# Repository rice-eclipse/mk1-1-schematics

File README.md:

# mk1-1-schematics
The official repository for mk1-1 pcb schematics for the Rice Eclipse Rocketry Club at Rice University.

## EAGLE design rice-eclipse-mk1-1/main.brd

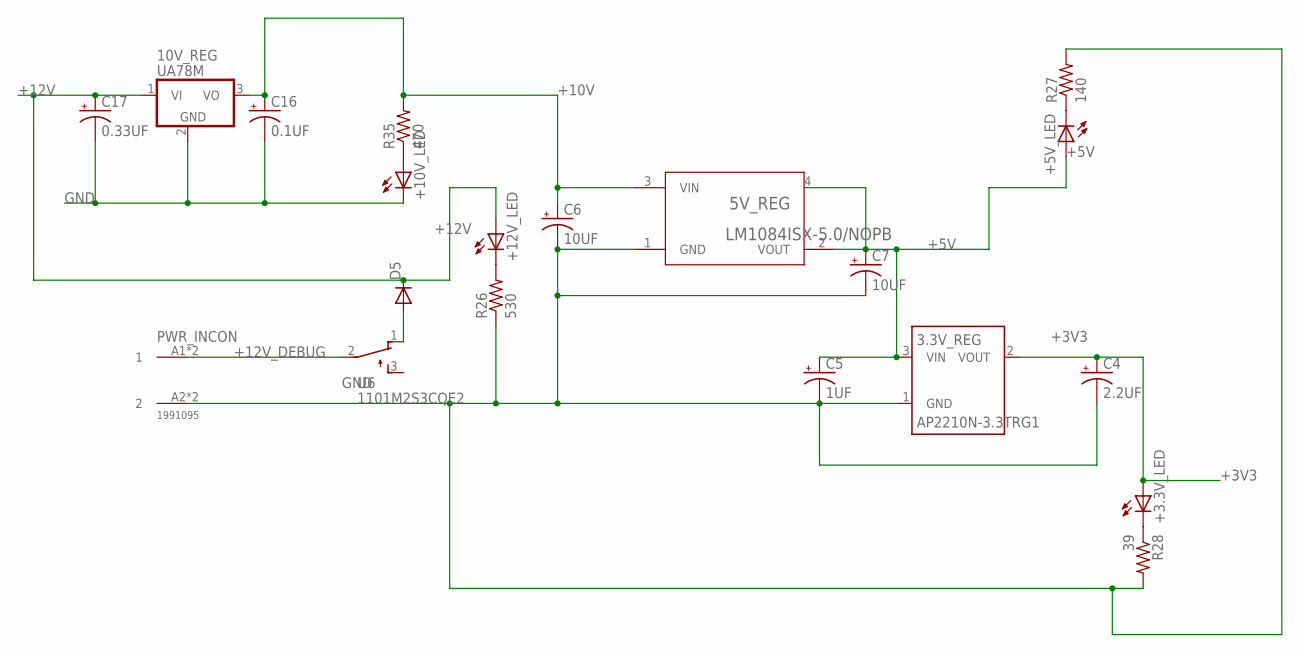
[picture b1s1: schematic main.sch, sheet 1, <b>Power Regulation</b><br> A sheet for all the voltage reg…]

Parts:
3.3V_REG: AP2210N-3.3TRG1; SOT23
5V_REG: LM1084ISX-5.0/NOPB; TS3B
10V_REG: UA78M; TO220S
+3.3V_LED, +5V_LED, +10V_LED, +12V_LED: LED5MM
C4: 2.2UF; E2,5-5
C5: 1UF; E2,5-5
C6, C7: 10UF; E2,5-5
C16: 0.1UF; E2,5-5
C17: 0.33UF; E2,5-5
D5: DIODE-DO201-15; DO201-15
PWR_IN: 1991095
R26: 530; R0805
R27: 140; R0805
R28: 39; R0805
R35: 470; R0805
U6: 1101M2S3CQE2

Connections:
+3V3: 3.3V_REG.2 (VOUT), +3.3V_LED.A, C4.+; also elsewhere on the board
+5V: 3.3V_REG.3 (VIN), 5V_REG.2 (VOUT), 5V_REG.4, +5V_LED.A, C5.+, C7.+; also elsewhere on the board
+10V: 5V_REG.3 (VIN), 10V_REG.3 (VO), C6.+, C16.+, R35.2; also elsewhere on the board
+12V: 10V_REG.1 (VI), +12V_LED.A, C17.+, D5.C; also elsewhere on the board
+12V_DEBUG: PWR_IN.A1 (1), PWR_IN.B1 (1), U6.2
GND: 3.3V_REG.1 (GND), 5V_REG.1 (GND), 10V_REG.2 (GND), +10V_LED.K (C), C4.-, C5.-, C6.-, C7.-, C16.-, C17.-, PWR_IN.A2 (2), PWR_IN.B2 (2), R26.1, R27.2, R28.2; also elsewhere on the board
unnamed: +12V_LED.K (C), R26.2
unnamed: +5V_LED.K (C), R27.1
unnamed: +3.3V_LED.K (C), R28.1
unnamed: D5.A, U6.1 (O)
unnamed: +10V_LED.A, R35.1

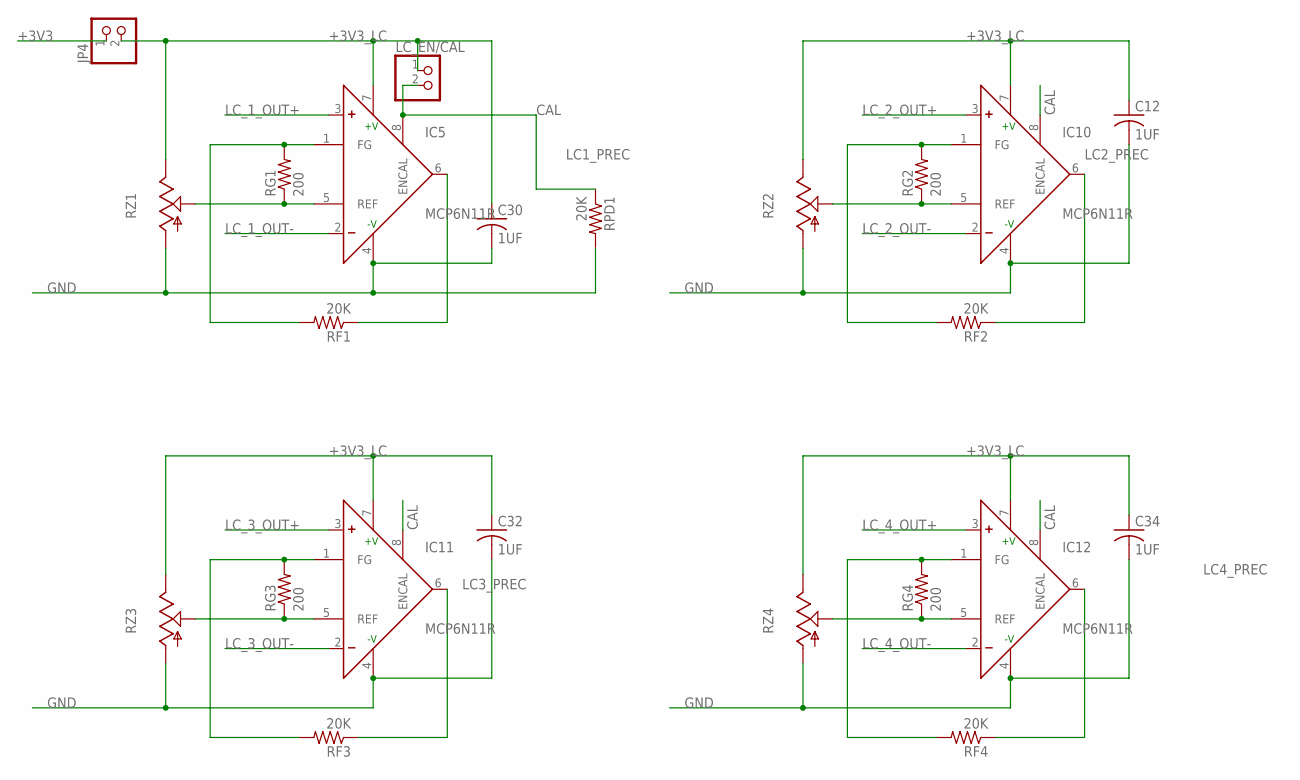
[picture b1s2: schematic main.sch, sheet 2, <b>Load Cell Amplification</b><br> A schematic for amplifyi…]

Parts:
C12, C30, C32, C34: 1UF; C0805
IC5, IC10, IC11, IC12: MCP6N11R; SO-8
JP4: PINHD-1X2; 1X02
LC_EN/CAL: PINHD-1X2; 1X02
RF1, RF2, RF3, RF4: 20K; R0805
RG1, RG2, RG3, RG4: 200; R0805
RPD1: 20K; R0805
RZ1, RZ2, RZ3, RZ4: TRIM_US-S64W; S64W

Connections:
+3V3: JP4.1; also elsewhere on the board
+3V3_LC: C12.1, C30.1, C32.1, C34.1, IC5.7 (+V), IC10.7 (+V), IC11.7 (+V), IC12.7 (+V), JP4.2, LC_EN/CAL.1, RZ1.E, RZ2.E, RZ3.E, RZ4.E
CAL: IC5.8 (ENCAL), IC10.8 (ENCAL), IC11.8 (ENCAL), IC12.8 (ENCAL), LC_EN/CAL.2, RPD1.1
GND: C12.2, C30.2, C32.2, C34.2, IC5.4 (-V), IC10.4 (-V), IC11.4 (-V), IC12.4 (-V), RPD1.2, RZ1.A, RZ2.A, RZ3.A, RZ4.A; also elsewhere on the board
LC1_PREC: IC5.6 (OUT), RF1.1; also elsewhere on the board
LC2_PREC: IC10.6 (OUT), RF2.1; also elsewhere on the board
LC3_PREC: IC11.6 (OUT), RF3.1; also elsewhere on the board
LC4_PREC: IC12.6 (OUT), RF4.1; also elsewhere on the board
LC_1_OUT+: IC5.3 (+); also elsewhere on the board
LC_1_OUT-: IC5.2 (-); also elsewhere on the board
LC_2_OUT+: IC10.3 (+); also elsewhere on the board
LC_2_OUT-: IC10.2 (-); also elsewhere on the board
LC_3_OUT+: IC11.3 (+); also elsewhere on the board
LC_3_OUT-: IC11.2 (-); also elsewhere on the board
LC_4_OUT+: IC12.3 (+); also elsewhere on the board
LC_4_OUT-: IC12.2 (-); also elsewhere on the board
unnamed: IC10.1 (FG), RF2.2, RG2.2
unnamed: IC10.5 (REF), RG2.1, RZ2.S
unnamed: IC11.1 (FG), RF3.2, RG3.2
unnamed: IC5.1 (FG), RF1.2, RG1.2
unnamed: IC5.5 (REF), RG1.1, RZ1.S
unnamed: IC11.5 (REF), RG3.1, RZ3.S
unnamed: IC12.1 (FG), RF4.2, RG4.2
unnamed: IC12.5 (REF), RG4.1, RZ4.S

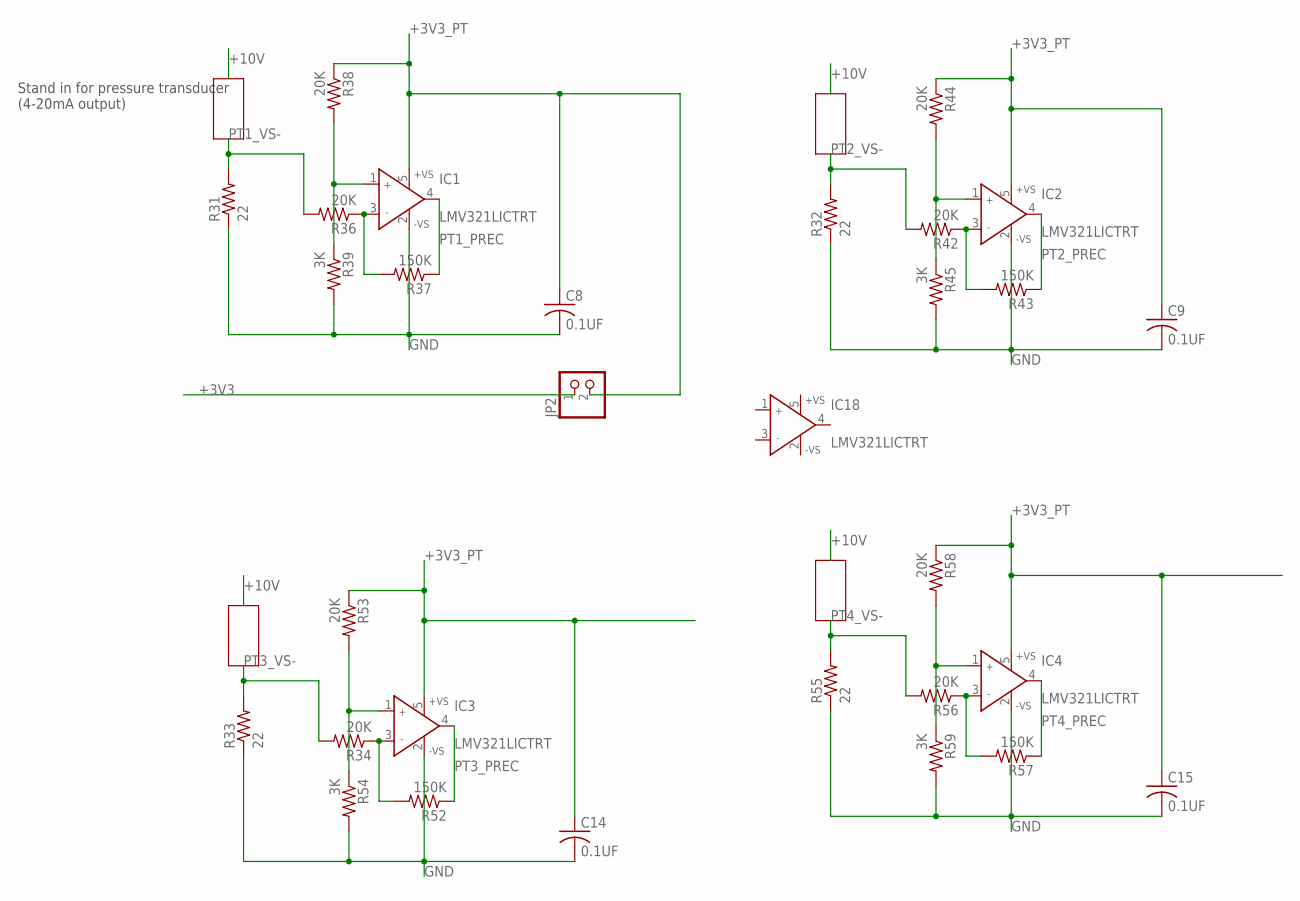
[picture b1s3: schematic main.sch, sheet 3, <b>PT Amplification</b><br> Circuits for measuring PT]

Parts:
C8, C9, C14, C15: 0.1UF; C0805
IC1, IC2, IC3, IC4, IC18: LMV321LICTRT; SOT23-5
JP2: PINHD-1X2; 1X02
R31, R32, R33, R55: 22; R0805
R34, R36, R38, R42, R44, R53, R56, R58: 20K; R0805
R37, R43, R52, R57: 150K; R0805
R39, R45, R54, R59: 3K; R0805

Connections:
+3V3: JP2.1; also elsewhere on the board
+3V3_PT: C8.1, C9.1, C14.1, C15.1, IC1.5 (+VS), IC2.5 (+VS), IC3.5 (+VS), IC4.5 (+VS), JP2.2, R38.1, R44.1, R53.1, R58.1
GND: C8.2, C9.2, C14.2, C15.2, IC1.2 (-VS), IC2.2 (-VS), IC3.2 (-VS), IC4.2 (-VS), R31.1, R32.1, R33.1, R39.2, R45.2, R54.2, R55.1, R59.2; also elsewhere on the board
unnamed: IC1.3 (IN-), R36.1, R37.2
unnamed: IC1.1 (IN+), R38.2, R39.1
unnamed: IC2.3 (IN-), R42.1, R43.2
unnamed: IC2.1 (IN+), R44.2, R45.1
unnamed: IC3.3 (IN-), R34.1, R52.2
unnamed: IC3.1 (IN+), R53.2, R54.1
unnamed: IC4.3 (IN-), R56.1, R57.2
unnamed: IC4.1 (IN+), R58.2, R59.1
PT1_PREC: IC1.4 (OUT), R37.1; also elsewhere on the board
PT1_VS-: R31.2, R36.2; also elsewhere on the board
PT2_PREC: IC2.4 (OUT), R43.1; also elsewhere on the board
PT2_VS-: R32.2, R42.2; also elsewhere on the board
PT3_PREC: IC3.4 (OUT), R52.1; also elsewhere on the board
PT3_VS-: R33.2, R34.2; also elsewhere on the board
PT4_PREC: IC4.4 (OUT), R57.1; also elsewhere on the board
PT4_VS-: R55.2, R56.2; also elsewhere on the board

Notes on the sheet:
Stand in for pressure transducer (4-20mA output)

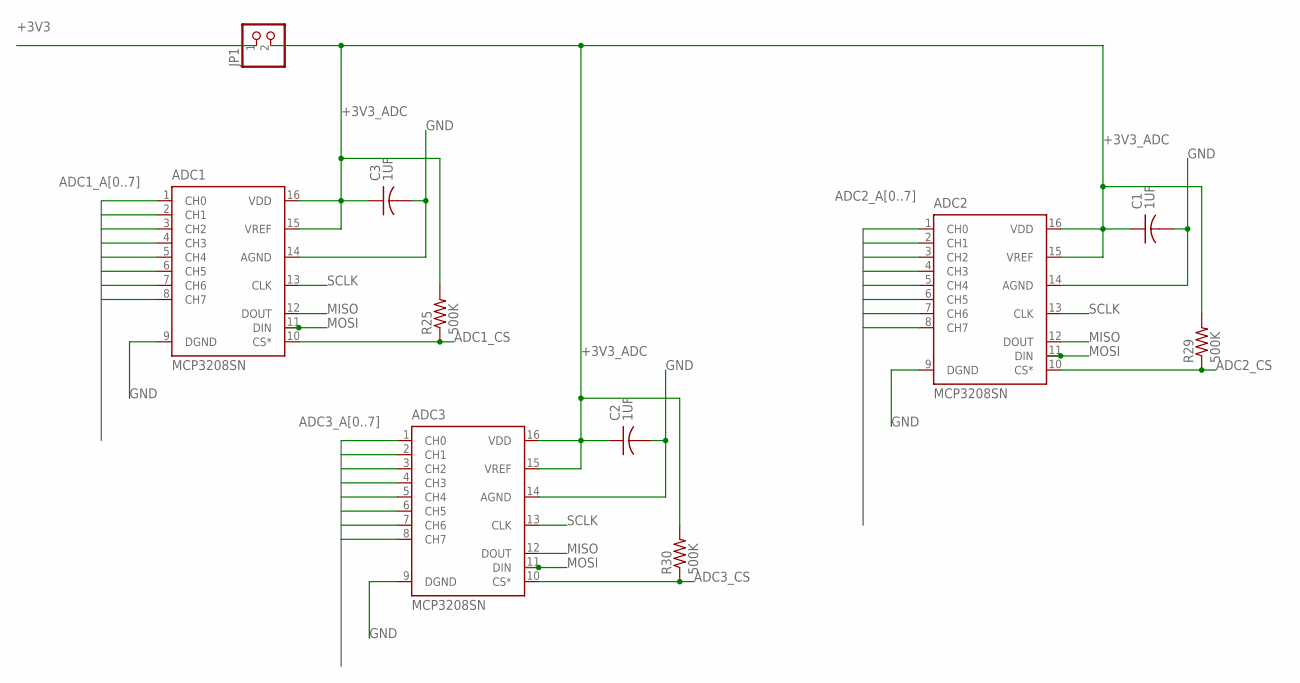
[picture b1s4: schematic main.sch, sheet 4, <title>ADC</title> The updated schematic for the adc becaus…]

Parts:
ADC1, ADC2, ADC3: MCP3208SN; SO-16
C1, C2, C3: 1UF; C0805
JP1: PINHD-1X2; 1X02
R25, R29, R30: 500K; R0805

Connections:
+3V3: JP1.1; also elsewhere on the board
+3V3_ADC: ADC1.15 (VREF), ADC1.16 (VDD), ADC2.15 (VREF), ADC2.16 (VDD), ADC3.15 (VREF), ADC3.16 (VDD), C1.1, C2.1, C3.1, JP1.2, R25.2, R29.2, R30.2
ADC1_A0: ADC1.1 (CH0); also elsewhere on the board
ADC1_A1: ADC1.2 (CH1); also elsewhere on the board
ADC1_A2: ADC1.3 (CH2); also elsewhere on the board
ADC1_A3: ADC1.4 (CH3); also elsewhere on the board
ADC1_A4: ADC1.5 (CH4); also elsewhere on the board
ADC1_A5: ADC1.6 (CH5); also elsewhere on the board
ADC1_A6: ADC1.7 (CH6); also elsewhere on the board
ADC1_A7: ADC1.8 (CH7); also elsewhere on the board
ADC1_CS: ADC1.10 (CS*), R25.1; also elsewhere on the board
ADC2_A0: ADC2.1 (CH0); also elsewhere on the board
ADC2_A1: ADC2.2 (CH1); also elsewhere on the board
ADC2_A2: ADC2.3 (CH2); also elsewhere on the board
ADC2_A3: ADC2.4 (CH3); also elsewhere on the board
ADC2_A4: ADC2.5 (CH4); also elsewhere on the board
ADC2_A5: ADC2.6 (CH5); also elsewhere on the board
ADC2_A6: ADC2.7 (CH6); also elsewhere on the board
ADC2_A7: ADC2.8 (CH7); also elsewhere on the board
ADC2_CS: ADC2.10 (CS*), R29.1; also elsewhere on the board
ADC3_A0: ADC3.1 (CH0); also elsewhere on the board
ADC3_A1: ADC3.2 (CH1); also elsewhere on the board
ADC3_A2: ADC3.3 (CH2); also elsewhere on the board
ADC3_A3: ADC3.4 (CH3); also elsewhere on the board
ADC3_A4: ADC3.5 (CH4); also elsewhere on the board
ADC3_A5: ADC3.6 (CH5); also elsewhere on the board
ADC3_A6: ADC3.7 (CH6); also elsewhere on the board
ADC3_A7: ADC3.8 (CH7); also elsewhere on the board
ADC3_CS: ADC3.10 (CS*), R30.1; also elsewhere on the board
GND: ADC1.9 (DGND), ADC1.14 (AGND), ADC2.9 (DGND), ADC2.14 (AGND), ADC3.9 (DGND), ADC3.14 (AGND), C1.2, C2.2, C3.2; also elsewhere on the board
MISO: ADC1.12 (DOUT), ADC2.12 (DOUT), ADC3.12 (DOUT); also elsewhere on the board
MOSI: ADC1.11 (DIN), ADC2.11 (DIN), ADC3.11 (DIN); also elsewhere on the board
SCLK: ADC1.13 (CLK), ADC2.13 (CLK), ADC3.13 (CLK); also elsewhere on the board

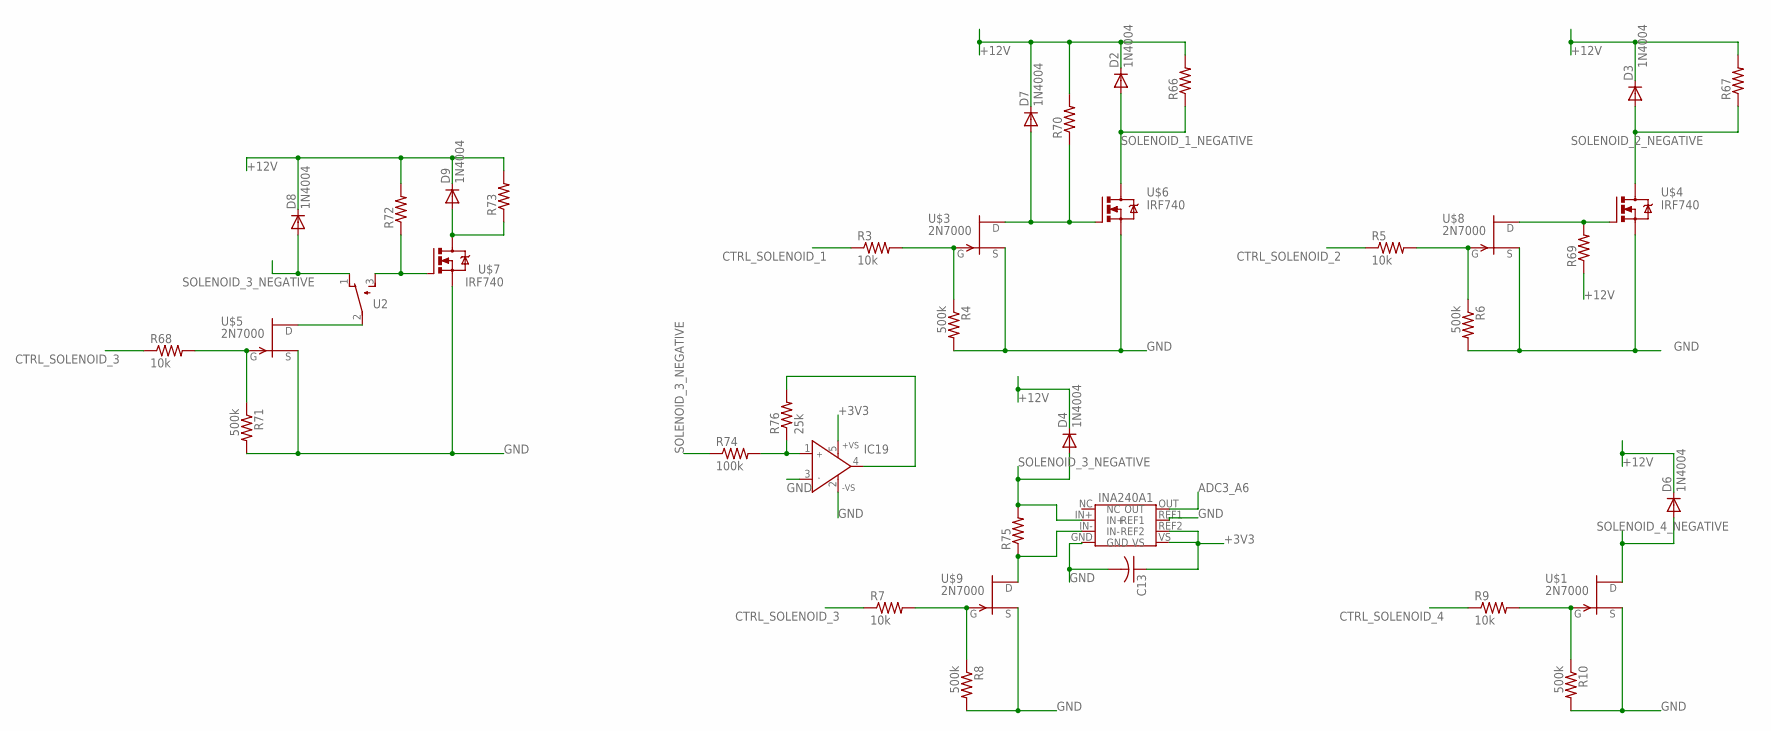
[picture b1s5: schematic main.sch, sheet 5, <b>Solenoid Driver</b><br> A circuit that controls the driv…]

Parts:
C13: C-USC0805; C0805
D2, D3, D4, D6, D7, D8, D9: 1N4004; DO41-10
IC19: LMV321LICTRT; SOT23-5
R3, R5, R7, R9, R68: 10k; R0805
R4, R6, R8, R10, R71: 500k; R0805
R66, R67, R69, R70, R72, R73: R-US_R0805; R0805
R74: 100k; R0805
R75: R-US_R0603; R0603
R76: 25k; R0805
U2: 1101M2S3CQE2
U$1, U$3, U$5, U$8, U$9: 2N7000; SOT23
U$4, U$6, U$7: IRF740; TO220BV
U$10: INA240A1

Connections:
+3V3: C13.1, IC19.5 (+VS), U$10.REF2, U$10.VS; also elsewhere on the board
+12V: D2.C, D3.C, D4.C, D6.C, D7.C, D8.C, D9.C, R66.2, R67.2, R69.1, R70.2, R72.2, R73.2; also elsewhere on the board
ADC3_A6: U$10.OUT; also elsewhere on the board
CTRL_SOLENOID_1: R3.1; also elsewhere on the board
CTRL_SOLENOID_2: R5.1; also elsewhere on the board
CTRL_SOLENOID_3: R7.1, R68.1; also elsewhere on the board
CTRL_SOLENOID_4: R9.1; also elsewhere on the board
GND: C13.2, IC19.2 (-VS), IC19.3 (IN-), R4.2, R6.2, R8.2, R10.2, R71.2, U$1.2 (S), U$3.2 (S), U$4.S, U$5.2 (S), U$6.S, U$7.S, U$8.2 (S), U$9.2 (S), U$10.GND, U$10.REF1; also elsewhere on the board
unnamed: R3.2, R4.1, U$3.1 (G)
unnamed: R5.2, R6.1, U$8.1 (G)
unnamed: R7.2, R8.1, U$9.1 (G)
unnamed: R9.2, R10.1, U$1.1 (G)
unnamed: D7.A, R70.1, U$3.3 (D), U$6.G
unnamed: R68.2, R71.1, U$5.1 (G)
unnamed: R69.2, U$4.G, U$8.3 (D)
unnamed: U2.2, U$5.3 (D)
unnamed: R72.1, U2.3 (S), U$7.G
unnamed: D9.A, R73.1, U$7.D
unnamed: R75.1, U$9.3 (D), U$10.IN-
unnamed: IC19.1 (IN+), R74.2, R76.1
unnamed: IC19.4 (OUT), R76.2
SOLENOID_1_NEGATIVE: D2.A, R66.1, U$6.D; also elsewhere on the board
SOLENOID_2_NEGATIVE: D3.A, R67.1, U$4.D; also elsewhere on the board
SOLENOID_3_NEGATIVE: D4.A, D8.A, R74.1, R75.2, U2.1 (O), U$10.IN+; also elsewhere on the board
SOLENOID_4_NEGATIVE: D6.A, U$1.3 (D); also elsewhere on the board

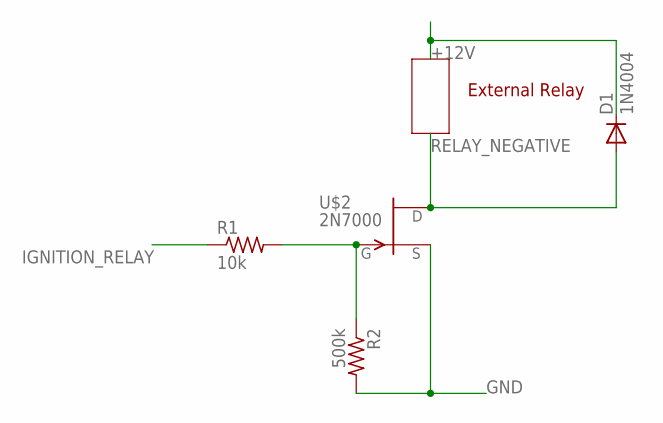
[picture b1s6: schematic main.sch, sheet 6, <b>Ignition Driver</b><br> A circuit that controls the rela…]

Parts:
D1: 1N4004; DO41-10
R1: 10k; R0805
R2: 500k; R0805
U$2: 2N7000; SOT23

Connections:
+12V: D1.C; also elsewhere on the board
GND: R2.2, U$2.2 (S); also elsewhere on the board
IGNITION_RELAY: R1.1; also elsewhere on the board
unnamed: R1.2, R2.1, U$2.1 (G)
RELAY_NEGATIVE: D1.A, U$2.3 (D); also elsewhere on the board

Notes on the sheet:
External Relay

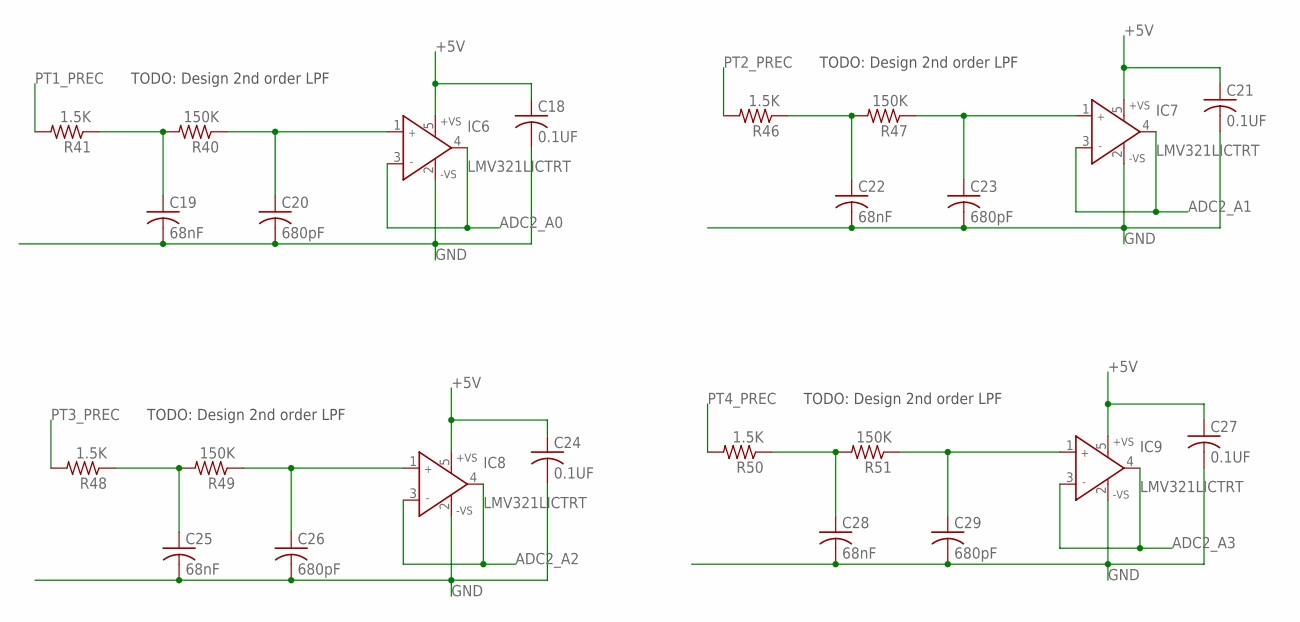
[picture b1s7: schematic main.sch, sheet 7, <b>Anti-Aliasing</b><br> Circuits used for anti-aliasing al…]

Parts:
C18, C21, C24, C27: 0.1UF; C0805
C19, C22, C25, C28: 68nF; C0805
C20, C23, C26, C29: 680pF; C0805
IC6, IC7, IC8, IC9: LMV321LICTRT; SOT23-5
R40, R47, R49, R51: 150K; R0805
R41, R46, R48, R50: 1.5K; R0805

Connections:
+5V: C18.1, C21.1, C24.1, C27.1, IC6.5 (+VS), IC7.5 (+VS), IC8.5 (+VS), IC9.5 (+VS); also elsewhere on the board
ADC2_A0: IC6.3 (IN-), IC6.4 (OUT); also elsewhere on the board
ADC2_A1: IC7.3 (IN-), IC7.4 (OUT); also elsewhere on the board
ADC2_A2: IC8.3 (IN-), IC8.4 (OUT); also elsewhere on the board
ADC2_A3: IC9.3 (IN-), IC9.4 (OUT); also elsewhere on the board
GND: C18.2, C19.2, C20.2, C21.2, C22.2, C23.2, C24.2, C25.2, C26.2, C27.2, C28.2, C29.2, IC6.2 (-VS), IC7.2 (-VS), IC8.2 (-VS), IC9.2 (-VS); also elsewhere on the board
unnamed: C19.1, R40.2, R41.1
unnamed: C20.1, IC6.1 (IN+), R40.1
unnamed: C22.1, R46.1, R47.2
unnamed: C23.1, IC7.1 (IN+), R47.1
unnamed: C25.1, R48.1, R49.2
unnamed: C26.1, IC8.1 (IN+), R49.1
unnamed: C28.1, R50.1, R51.2
unnamed: C29.1, IC9.1 (IN+), R51.1
PT1_PREC: R41.2; also elsewhere on the board
PT2_PREC: R46.2; also elsewhere on the board
PT3_PREC: R48.2; also elsewhere on the board
PT4_PREC: R50.2; also elsewhere on the board

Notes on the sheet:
TODO: Design 2nd order LPF

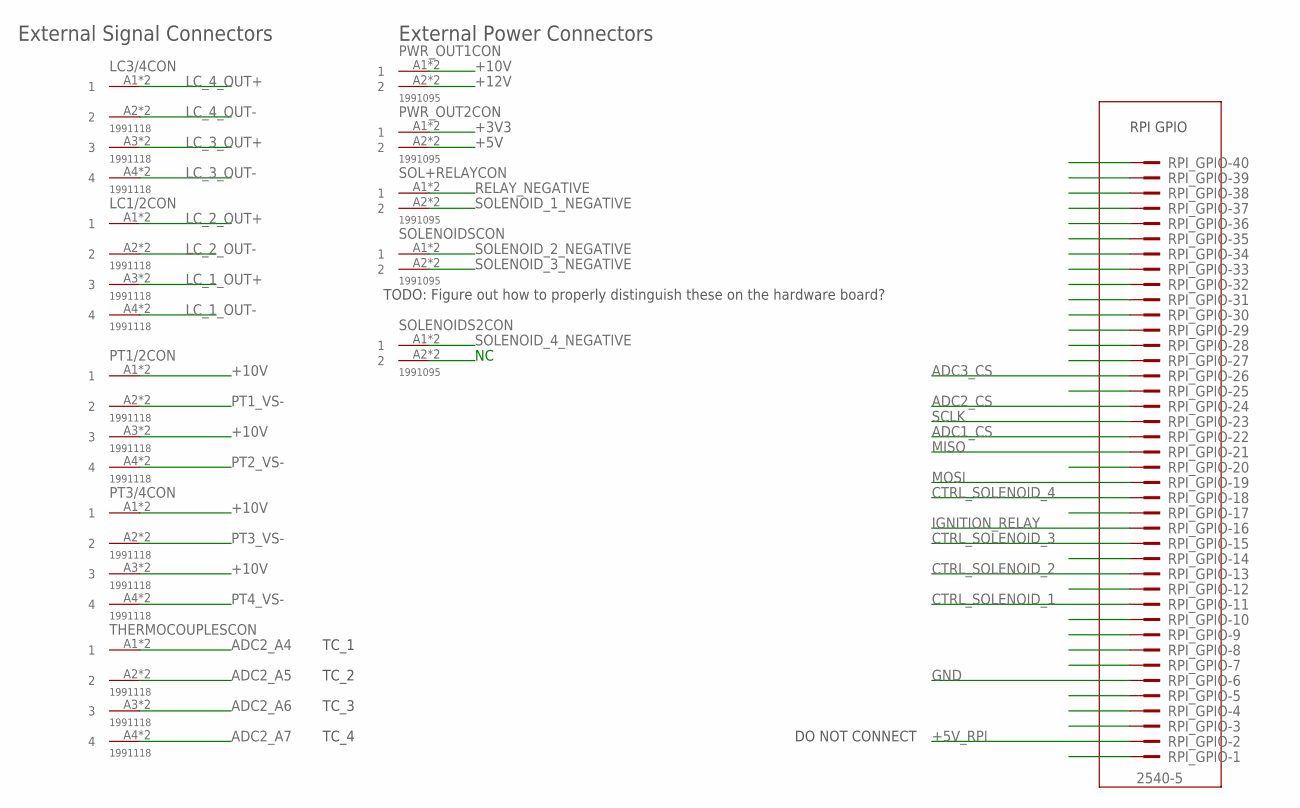
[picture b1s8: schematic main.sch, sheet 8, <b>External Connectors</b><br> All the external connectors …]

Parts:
LC1/2, LC3/4: 1991118
PT1/2, PT3/4: 1991118
PWR_OUT1, PWR_OUT2: 1991095
RPI_GPIO: 2540-5; PAK100/2500-5-40
SOL+RELAY: 1991095
SOLENOIDS, SOLENOIDS2: 1991095
THERMOCOUPLES: 1991118

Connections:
+3V3: PWR_OUT2.A1 (1), PWR_OUT2.B1 (1); also elsewhere on the board
+5V: PWR_OUT2.A2 (2), PWR_OUT2.B2 (2); also elsewhere on the board
+5V_RPI: RPI_GPIO.2
+10V: PT1/2.A1 (1), PT1/2.A3 (3), PT1/2.B1 (1), PT1/2.B3 (3), PT3/4.A1 (1), PT3/4.A3 (3), PT3/4.B1 (1), PT3/4.B3 (3), PWR_OUT1.A1 (1), PWR_OUT1.B1 (1); also elsewhere on the board
+12V: PWR_OUT1.A2 (2), PWR_OUT1.B2 (2); also elsewhere on the board
ADC1_CS: RPI_GPIO.22; also elsewhere on the board
ADC2_A4: THERMOCOUPLES.A1 (1), THERMOCOUPLES.B1 (1); also elsewhere on the board
ADC2_A5: THERMOCOUPLES.A2 (2), THERMOCOUPLES.B2 (2); also elsewhere on the board
ADC2_A6: THERMOCOUPLES.A3 (3), THERMOCOUPLES.B3 (3); also elsewhere on the board
ADC2_A7: THERMOCOUPLES.A4 (4), THERMOCOUPLES.B4 (4); also elsewhere on the board
ADC2_CS: RPI_GPIO.24; also elsewhere on the board
ADC3_CS: RPI_GPIO.26; also elsewhere on the board
CTRL_SOLENOID_1: RPI_GPIO.11; also elsewhere on the board
CTRL_SOLENOID_2: RPI_GPIO.13; also elsewhere on the board
CTRL_SOLENOID_3: RPI_GPIO.15; also elsewhere on the board
CTRL_SOLENOID_4: RPI_GPIO.18; also elsewhere on the board
GND: RPI_GPIO.6; also elsewhere on the board
IGNITION_RELAY: RPI_GPIO.16; also elsewhere on the board
LC_1_OUT+: LC1/2.A3 (3), LC1/2.B3 (3); also elsewhere on the board
LC_1_OUT-: LC1/2.A4 (4), LC1/2.B4 (4); also elsewhere on the board
LC_2_OUT+: LC1/2.A1 (1), LC1/2.B1 (1); also elsewhere on the board
LC_2_OUT-: LC1/2.A2 (2), LC1/2.B2 (2); also elsewhere on the board
LC_3_OUT+: LC3/4.A3 (3), LC3/4.B3 (3); also elsewhere on the board
LC_3_OUT-: LC3/4.A4 (4), LC3/4.B4 (4); also elsewhere on the board
LC_4_OUT+: LC3/4.A1 (1), LC3/4.B1 (1); also elsewhere on the board
LC_4_OUT-: LC3/4.A2 (2), LC3/4.B2 (2); also elsewhere on the board
MISO: RPI_GPIO.21; also elsewhere on the board
MOSI: RPI_GPIO.19; also elsewhere on the board
unnamed: SOLENOIDS2.A2 (2), SOLENOIDS2.B2 (2)
PT1_VS-: PT1/2.A2 (2), PT1/2.B2 (2); also elsewhere on the board
PT2_VS-: PT1/2.A4 (4), PT1/2.B4 (4); also elsewhere on the board
PT3_VS-: PT3/4.A2 (2), PT3/4.B2 (2); also elsewhere on the board
PT4_VS-: PT3/4.A4 (4), PT3/4.B4 (4); also elsewhere on the board
RELAY_NEGATIVE: SOL+RELAY.A1 (1), SOL+RELAY.B1 (1); also elsewhere on the board
RPI_GPIO_1: RPI_GPIO.1
RPI_GPIO_3: RPI_GPIO.3
RPI_GPIO_4: RPI_GPIO.4
RPI_GPIO_5: RPI_GPIO.5
RPI_GPIO_7: RPI_GPIO.7
RPI_GPIO_8: RPI_GPIO.8
RPI_GPIO_9: RPI_GPIO.9
RPI_GPIO_10: RPI_GPIO.10
RPI_GPIO_12: RPI_GPIO.12
RPI_GPIO_14: RPI_GPIO.14
RPI_GPIO_17: RPI_GPIO.17
RPI_GPIO_20: RPI_GPIO.20
RPI_GPIO_25: RPI_GPIO.25
RPI_GPIO_27: RPI_GPIO.27
RPI_GPIO_28: RPI_GPIO.28
RPI_GPIO_29: RPI_GPIO.29
RPI_GPIO_30: RPI_GPIO.30
RPI_GPIO_31: RPI_GPIO.31
RPI_GPIO_32: RPI_GPIO.32
RPI_GPIO_33: RPI_GPIO.33
RPI_GPIO_34: RPI_GPIO.34
RPI_GPIO_35: RPI_GPIO.35
RPI_GPIO_36: RPI_GPIO.36
RPI_GPIO_37: RPI_GPIO.37
RPI_GPIO_38: RPI_GPIO.38
RPI_GPIO_39: RPI_GPIO.39
RPI_GPIO_40: RPI_GPIO.40
SCLK: RPI_GPIO.23; also elsewhere on the board
SOLENOID_1_NEGATIVE: SOL+RELAY.A2 (2), SOL+RELAY.B2 (2); also elsewhere on the board
SOLENOID_2_NEGATIVE: SOLENOIDS.A1 (1), SOLENOIDS.B1 (1); also elsewhere on the board
SOLENOID_3_NEGATIVE: SOLENOIDS.A2 (2), SOLENOIDS.B2 (2); also elsewhere on the board
SOLENOID_4_NEGATIVE: SOLENOIDS2.A1 (1), SOLENOIDS2.B1 (1); also elsewhere on the board

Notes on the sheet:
RPI GPIO
External Signal Connectors
External Power Connectors
TODO: Figure out how to properly distinguish these on the hardware board?
TC_1
TC_2
TC_3
TC_4
DO NOT CONNECT

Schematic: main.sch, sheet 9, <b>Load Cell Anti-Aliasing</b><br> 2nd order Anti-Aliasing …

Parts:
C10, C37, C40, C43, C46: 0.1UF; C0805
C11, C36, C38, C39, C41, C42, C44, C45: 1nF; C0805
C47, C48: ?; C0805
IC13, IC14, IC15, IC16, IC17: LMV321LICTRT; SOT23-5
LC1, LC2, LC3, LC4, LC5: PINHD-1X2; 1X02
LCAA_EN: PINHD-1X2; 1X02
LCIN1, LCIN2, LCIN3, LCIN4, LCIN5: PINHD-1X2; 1X02
R11, R15, R19, R23: 24.7K; R0805
R12, R16, R20, R24: 164K; R0805
R13, R17, R21, R60: 50.6K; R0805
R14, R18, R22, R61: 12.6K; R0805
R62, R63, R64, R65: ?; R0805

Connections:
+3V3: LCAA_EN.1; also elsewhere on the board
+3V3_LCAA: C10.1, IC13.5 (+VS), LCAA_EN.2
+5V_LCAA: C37.1, C40.1, C43.1, C46.1, IC14.5 (+VS), IC15.5 (+VS), IC16.5 (+VS), IC17.5 (+VS)
ADC1_A0: LC1.1; also elsewhere on the board
ADC1_A1: LC2.1; also elsewhere on the board
ADC1_A3: LC3.1; also elsewhere on the board
ADC1_A4: LC4.1; also elsewhere on the board
ADC1_A5: LC5.1; also elsewhere on the board
GND: C10.2, C36.2, C37.2, C38.2, C40.2, C41.2, C43.2, C44.2, C46.2, C47.2, IC13.2 (-VS), IC14.2 (-VS), IC15.2 (-VS), IC16.2 (-VS), IC17.2 (-VS), R14.2, R18.2, R22.2, R61.2, R65.2; also elsewhere on the board
LC1_PREC: LCIN1.2; also elsewhere on the board
LC2_PREC: LCIN2.2; also elsewhere on the board
LC3_PREC: LCIN3.2; also elsewhere on the board
LC4_PREC: LCIN4.2; also elsewhere on the board
unnamed: C11.1, R11.1, R12.2
unnamed: C36.1, IC13.1 (IN+), R12.1
unnamed: C39.1, R15.1, R16.2
unnamed: C11.2, IC13.4 (OUT), LC1.2, R13.1
unnamed: C38.1, IC14.1 (IN+), R16.1
unnamed: C39.2, IC14.4 (OUT), LC2.2, R17.1
unnamed: IC14.3 (IN-), R17.2, R18.1
unnamed: C42.1, R19.1, R20.2
unnamed: C41.1, IC15.1 (IN+), R20.1
unnamed: C42.2, IC15.4 (OUT), LC3.2, R21.1
unnamed: IC15.3 (IN-), R21.2, R22.1
unnamed: C45.1, R23.1, R24.2
unnamed: C44.1, IC16.1 (IN+), R24.1
unnamed: C45.2, IC16.4 (OUT), LC4.2, R60.1
unnamed: IC13.3 (IN-), R13.2, R14.1
unnamed: IC16.3 (IN-), R60.2, R61.1
unnamed: LCIN1.1, R11.2
unnamed: LCIN2.1, R15.2
unnamed: LCIN3.1, R19.2
unnamed: LCIN4.1, R23.2
unnamed: C48.1, R62.1, R63.2
unnamed: C47.1, IC17.1 (IN+), R63.1
unnamed: C48.2, IC17.4 (OUT), LC5.2, R64.1
unnamed: IC17.3 (IN-), R64.2, R65.1
unnamed: LCIN5.1, R62.2

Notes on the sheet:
2nd order Butterworth Lowpass Filter. Gain 5V/V, Cutoff 2.5KHz
Alternately selectable Filter stage that can be used for MK2

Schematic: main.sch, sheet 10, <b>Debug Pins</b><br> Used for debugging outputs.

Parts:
PWR_DEBUG: MPT5; 5POL254
RPI_DEBUG: MPT7; 7POL254
X4, X7, X8: MPT8; 8POL254

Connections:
+3V3: PWR_DEBUG.4; also elsewhere on the board
+5V: PWR_DEBUG.3; also elsewhere on the board
+10V: PWR_DEBUG.2; also elsewhere on the board
+12V: PWR_DEBUG.1; also elsewhere on the board
ADC1_A0: X4.1; also elsewhere on the board
ADC1_A1: X4.2; also elsewhere on the board
ADC1_A2: X4.3; also elsewhere on the board
ADC1_A3: X4.4; also elsewhere on the board
ADC1_A4: X4.5; also elsewhere on the board
ADC1_A5: X4.6; also elsewhere on the board
ADC1_A6: X4.7; also elsewhere on the board
ADC1_A7: X4.8; also elsewhere on the board
ADC1_CS: RPI_DEBUG.4; also elsewhere on the board
ADC2_A0: X7.1; also elsewhere on the board
ADC2_A1: X7.2; also elsewhere on the board
ADC2_A2: X7.3; also elsewhere on the board
ADC2_A3: X7.4; also elsewhere on the board
ADC2_A4: X7.5; also elsewhere on the board
ADC2_A5: X7.6; also elsewhere on the board
ADC2_A6: X7.7; also elsewhere on the board
ADC2_A7: X7.8; also elsewhere on the board
ADC2_CS: RPI_DEBUG.3; also elsewhere on the board
ADC3_A0: X8.1; also elsewhere on the board
ADC3_A1: X8.2; also elsewhere on the board
ADC3_A2: X8.3; also elsewhere on the board
ADC3_A3: X8.4; also elsewhere on the board
ADC3_A4: X8.5; also elsewhere on the board
ADC3_A5: X8.6; also elsewhere on the board
ADC3_A6: X8.7; also elsewhere on the board
ADC3_A7: X8.8; also elsewhere on the board
ADC3_CS: RPI_DEBUG.2; also elsewhere on the board
GND: PWR_DEBUG.5, RPI_DEBUG.1; also elsewhere on the board
MISO: RPI_DEBUG.6; also elsewhere on the board
MOSI: RPI_DEBUG.5; also elsewhere on the board
SCLK: RPI_DEBUG.7; also elsewhere on the board

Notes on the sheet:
ADC_1 Debug pins

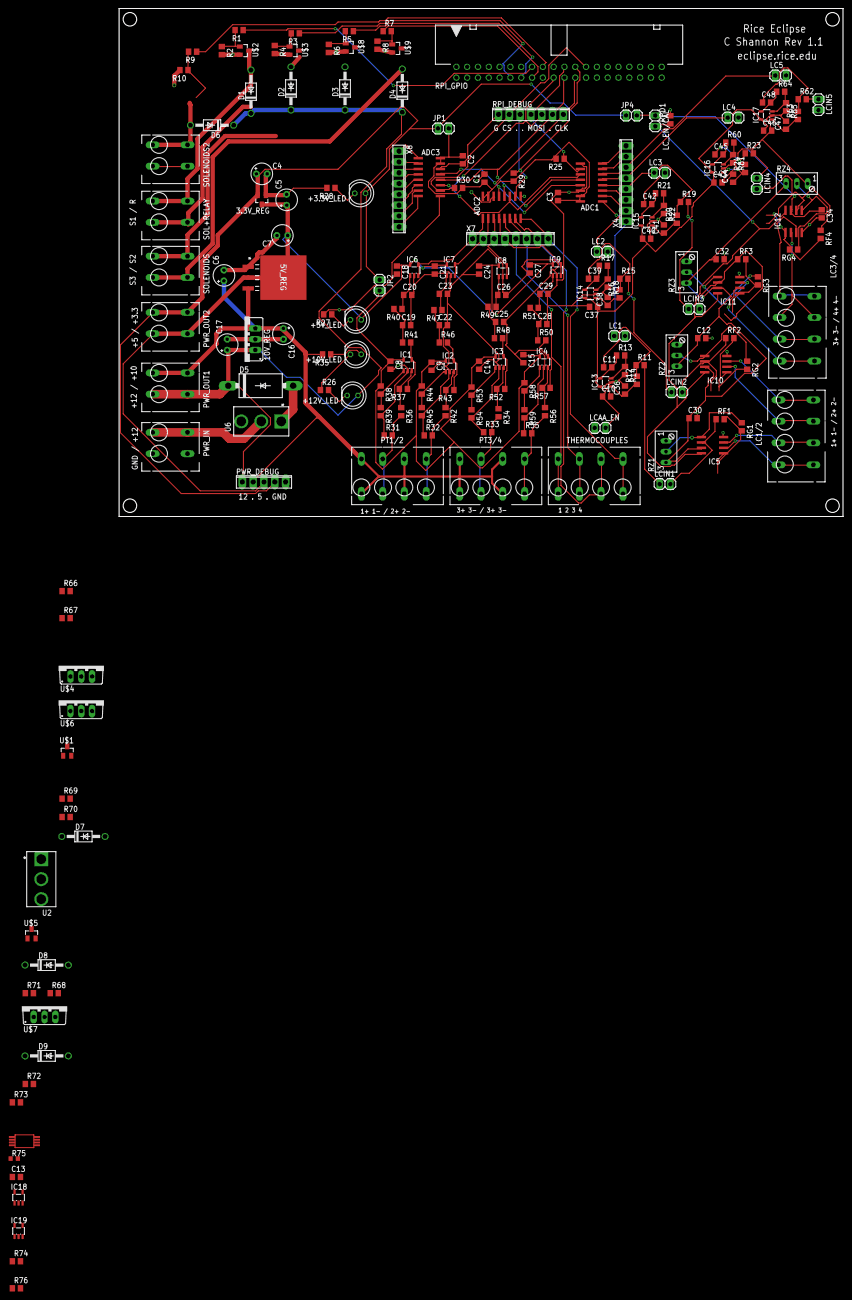
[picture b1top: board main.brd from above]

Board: 2 copper layers, 170.1 x 119.4 mm, 216 parts (0 on the bottom side), 141 nets.

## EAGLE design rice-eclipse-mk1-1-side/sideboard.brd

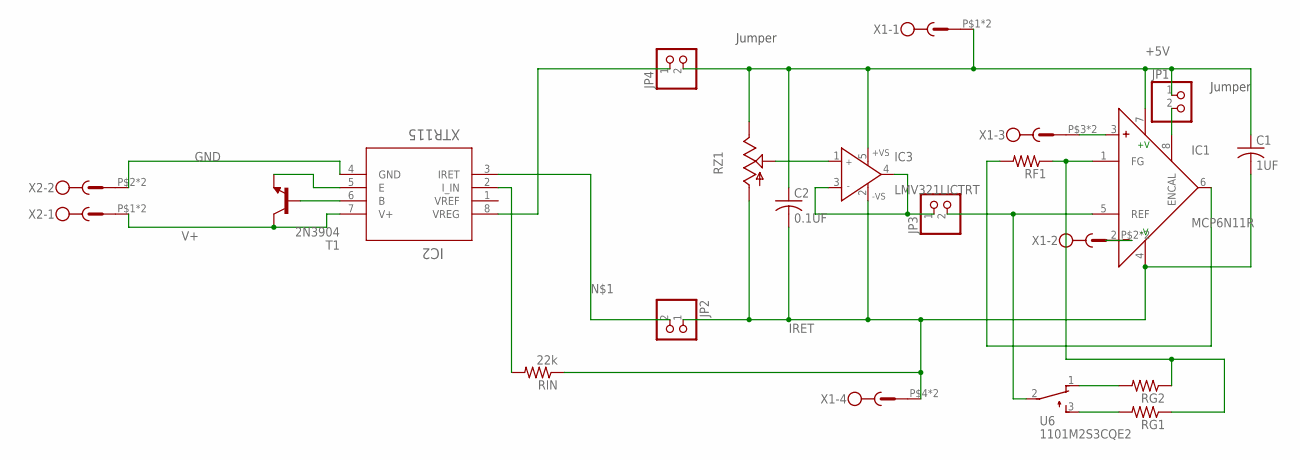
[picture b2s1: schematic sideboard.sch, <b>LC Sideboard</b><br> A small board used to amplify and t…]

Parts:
C1: 1UF; C0603
C2: 0.1UF; C0603
IC1: MCP6N11R; SO-8
IC2: XTR115; SO-8
IC3: LMV321LICTRT; SOT23-5
JP1, JP2, JP3, JP4: PINHD-1X2; 1X02
RF1: R-US_0204/7; 0204/7
RG1, RG2: R-US_0204/7; 0204/7
RIN: 22k; 0204/7
RZ1: TRIM_US-S64W; S64W
T1: 2N3904; TO92
U6: 1101M2S3CQE2
X1, X2: 1770908

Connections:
+5V: C1.1, C2.1, IC1.7 (+V), IC3.5 (+VS), JP1.1, JP4.2, RZ1.E, X1.P$1, X1.P$5
GND: IC2.4 (GND), X2.P$2, X2.P$6
IRET: C1.2, C2.2, IC1.4 (-V), IC3.2 (-VS), JP2.1, RIN.1, RZ1.A, X1.P$4, X1.P$8
unnamed: IC2.3 (IRET), JP2.2
unnamed: IC2.2 (I_IN), RIN.2
unnamed: IC2.8 (VREG), JP4.1
unnamed: IC1.6 (OUT), RF1.2
unnamed: IC1.8 (ENCAL), JP1.2
unnamed: IC2.5 (E), T1.3 (E)
unnamed: IC1.1 (FG), RF1.1, RG1.1, RG2.1
unnamed: RG2.2, U6.1 (O)
unnamed: IC2.6 (B), T1.2 (B)
unnamed: IC1.3 (+), X1.P$3, X1.P$7
unnamed: IC1.2 (-), X1.P$2, X1.P$6
unnamed: RG1.2, U6.3 (S)
unnamed: IC3.1 (IN+), RZ1.S
unnamed: IC1.5 (REF), JP3.2, U6.2
unnamed: IC3.3 (IN-), IC3.4 (OUT), JP3.1
V+: IC2.7 (V+), T1.1 (C), X2.P$1, X2.P$5

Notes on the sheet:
Jumper

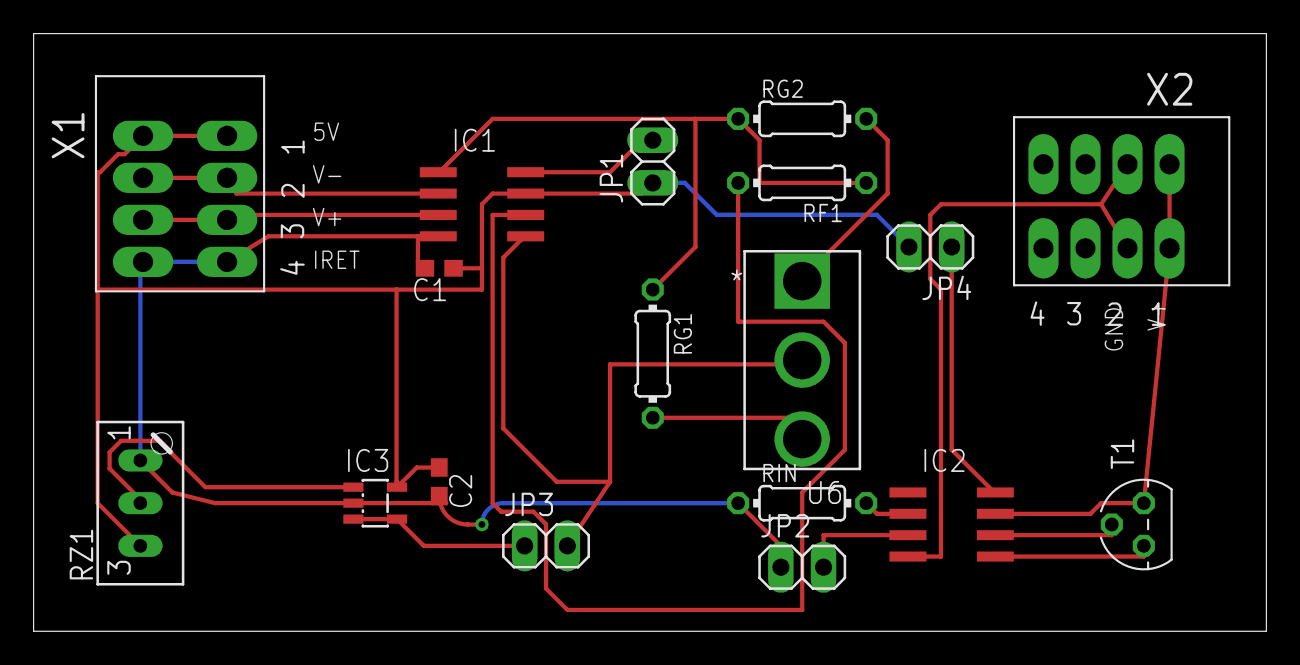
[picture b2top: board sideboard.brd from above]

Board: 2 copper layers, 73.3 x 35.5 mm, 18 parts (0 on the bottom side), 19 nets.

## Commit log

2017-08-24 Added the eagle files and configured them for proper use. Added an empty software folder for now.
2017-08-25 Added a new library for our 3.3V regulator. Fixed library backups in eagle .gitignore.
2017-08-31 Added some new voltage regulators and used them. I also did something else, but I'm not sure what it was.
2017-09-02 Added a shorts library and some skeleton sheets in the schematic. Should provide a good environment for working on project.
2017-09-03 Added voltage regulator for -0.23v
2017-09-04 edited wire
2017-09-07 Added a skeleton software setup.
    Includes a blink, and a dummy build that exit.
    Use cmake to just build them all and then run the one you want.
2017-09-07 Fixed the gitignore to remove a ".lck" file.
2017-09-09 Added relay and solenoid driver stuff
2017-09-09 Added a new sheet for external connectors.
    Added raspberry PI GPIO to the sheet.
    Will probably add any outputs and inputs soon.
2017-09-09 Tweaked name of a wire.
2017-09-11 Added a bunch of libraries to eagle and added some stuff.
    Fixed double pins on phoenix 500 library item.
    Added signal connectors to eagle libs.
    Added op-amp to texas lib.
    Added some headers to listener.
2017-09-14 Added external connectors and basic load cell amp.
2017-09-21 Added a 2 gang potentiometer for the gain tuning on load cell.
2017-09-22 Created a new build target for an adc abstraction.
2017-09-30 finished load cell circuit copied it over
    ya
2017-10-07 rotated capacitors
2017-10-11 Cleaned up placement on the board. Router scares me.
2017-10-12 Added a new 4-pin signal connector. Also modified board.
2017-10-12 Added RPI GPIO connections.
2017-10-15 EAGLE stuff
    - changed 6 pin connectors to 4 pin for loadcells 1-4
    - deleted load cell 5 connector
    - added debugging slide switches
    - board rearranged
2017-10-15 Eagle Stuff
    changed 5v_debug to 5v
2017-10-21 Added test LEDs for schematic.
    LEDs allow for test of current.
2017-10-21 Deleted LEDS to resync board
2017-10-21 Added new libraries and fixed board annotation.
    LEDS had to be removed in the process. Will re-add in next
    version. I'm mostly just happy that the board is fixed.
2017-10-22 Added to the LEDs
2017-10-22 Cleaned up the board, added adcs, debug pins.
2017-10-22 Added more board parts.
2017-10-26 Added initial PT circuit guess and
    added some routes for power.
2017-10-26 Slightly increased size of power traces.
2017-10-29 Made a bunch of stuff.
2017-10-29 Added flyback diodes and moved stuff onto board.
2017-10-29 Added schottky diode.
2017-10-29 Added some stuff.
2017-10-29 Board is ready to route.
2017-10-29 Routed power traces. Autorouter starts next.
2017-10-30 Routed and messed with text.
2017-10-30 Routed and tried to gen board.
    Fixed cap sizes too.
2017-11-19 Added sideboard.
2017-11-19 Added and routed.
2017-11-19 Rerouted with more stuff.
2018-01-20 Removed some profanity and clarified a couple documentation pieces. Also added a start of a logger, but I doubt it works or even compiles.
2018-01-20 Initial commit after splitting repository.
    * Renamed folders for consistency.
    * Tweaked README
2018-04-01 Fixed board files maybe.
2018-04-01 Fixed major known bugs in board design.
    * 5V power rail for AA voltage follower.
    * 10V rail to power PT connector.
2018-04-01 Added the 4 pin connector for the phoenix library.
2018-04-05 Added our library to Eagle. Updated the LC circuit.
2018-04-05 Minor improvements to board.
2018-04-06 Moved onto board. Preliminary power routing.
2018-04-06 Added AA filter to lowpass output.
2018-04-06 Updated board route a bit. Rest is autorouted.
2018-04-06 Added final routing for version 1.1.
2018-12-14 New schematics for Titan amp
2019-01-13 Fixed some routing and minor mistakes with the underlying circuit.
    TODO: still want to drill holes in the board.
2019-03-14 Make files match IRL
    - Fix jumpers to take output of the op amp
    directly, instead of across a resistor
    - Changed adc inputs to 3.3V from 5V
    - Added larger mosfets for TVC valves,
    need to double check though.
    Todo:
2019-03-16 Add mosfet driver circuit
    Currently have a version with a switch for using either
    the 2N7000 or IRF740 (high current). Might be useful to
    have a high current option for all the outputs since
    propulsion seems to like adding more high-current valves.
2019-03-16 Add library for INA240A1 current-sense amp
2019-03-16 Add current and voltage sense circuitry

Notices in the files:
parts and their libraries:
COPYRIGHT: Copyright (C) 2015 Accelerated Designs. All rights reserved
